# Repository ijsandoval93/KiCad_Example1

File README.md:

# KiCad_Example1
First attempt at learning KiCad and making PCB

In this respository, you will see all the files regarding the creation of my first PCB design and layout.

Current, I am investigating as to why my models did not move over when importing the 'Inverter' and 'AND' ICs.

This is a device that thats 5V and uses the dip switches to turn on and off differnet colored LEDs along with a buzzer.

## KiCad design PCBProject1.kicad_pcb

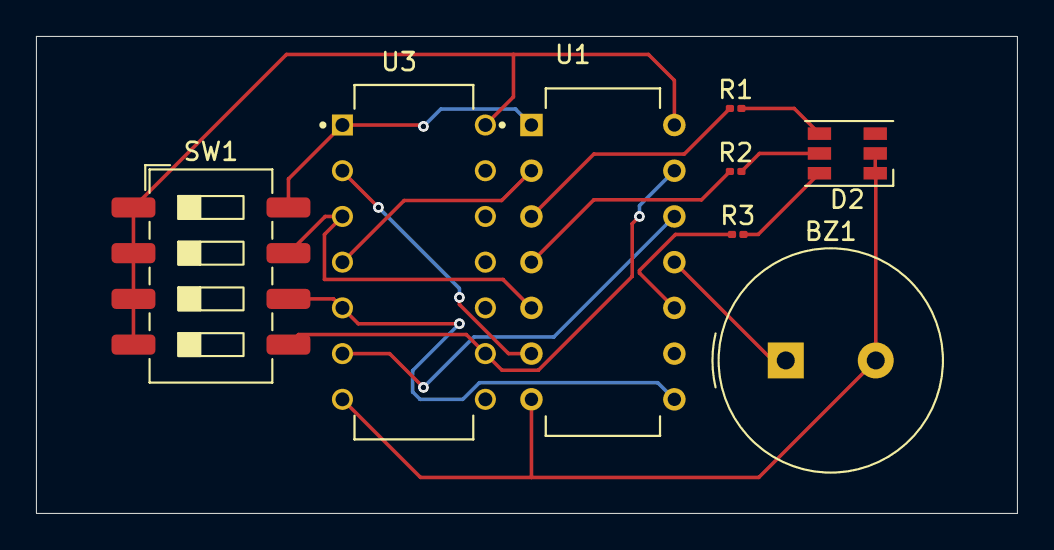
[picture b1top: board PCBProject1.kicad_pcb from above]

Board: 2 copper layers, 54.5 x 26.5 mm, 8 parts (0 on the bottom side), 17 nets.

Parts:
BZ1: Buzzer; Buzzer_TDK_PS1240P02BT_D12.2mm_H6.5mm
D2: LED_RGB; LED_RGB_PLCC-6
R1, R2, R3: 220; R_0201_0603Metric
SW1: SW_DIP_x04; SW_DIP_SPSTx04_Slide_6.7x11.72mm_W8.61mm_P2.54mm_LowProfile
U1: CD4081BE; DIP794W45P254L1930H508Q14
U3: SN74AC14N; DIP794W45P254L1969H508Q14

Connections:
+5V: SW1.1, SW1.2, SW1.3, SW1.4, U1.14 (VDD), U3.14 (VCC)
GND: BZ1.2 (-), D2.1 (RK), D2.2 (GK), D2.3 (BK), U1.7 (VSS), U3.7 (GND)
unnamed: BZ1.1 (+), U1.11 (M=G.H)
unnamed: D2.4 (BA), R1.2
unnamed: D2.5 (GA), R2.2
unnamed: D2.6 (RA), R3.2
unnamed: SW1.8, U1.1 (A), U3.1 (1A)
unnamed: U1.2 (B), U3.4 (2Y)
unnamed: SW1.7, U1.5 (C), U3.3 (2A)
unnamed: U1.6 (D), U3.2 (1Y)
unnamed: SW1.6, U1.8 (E), U3.5 (3A)
unnamed: U1.9 (F), U3.8 (4Y)
unnamed: U1.12 (G), U3.6 (3Y)
unnamed: SW1.5, U1.13 (H), U3.9 (4A)
unnamed: R1.1, U1.3 (J=A.B)
unnamed: R2.1, U1.4 (K=C.D)
unnamed: R3.1, U1.10 (L=E.F)
